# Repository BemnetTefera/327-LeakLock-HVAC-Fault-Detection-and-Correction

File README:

# LeakLock – Smart HVAC Fault Detection & Correction System

**LeakLock** is a low-cost, real-time HVAC monitoring solution that detects air duct leaks and corrects airflow across a three-zone system. Built with an ESP32, distributed sensors, and a web interface, it combines embedded systems, IoT, and sustainable design principles to solve a real-world energy efficiency problem.

---

## 🔧 Features

- 📶 Wi-Fi-enabled ESP32 microcontroller
- 🌡️ Real-time temperature and pressure sensing
- 🌀 Dual fan and motorized damper control
- 🖥️ Custom web interface using HTML, CSS, and JavaScript
- 🔄 OTA (Over-the-Air) updates for remote firmware management
- 🧩 PCB design files for sensor integration
- 📦 Total cost under $50

---

## 📁 Repository Structure

| File/Folder              | Description                                       |
|--------------------------|---------------------------------------------------|
| `index.html`             | Web interface frontend                           |
| `style.css`              | Styling for the frontend                         |
| `server.py`              | Tornado-based WebSocket server backend           |
| `main.cpp`               | ESP32 firmware: sensor reading & motor control   |
| `wifi_manager.cpp/h`     | Wi-Fi connection handler                         |
| `sensor_final_v1.brd`    | PCB board layout (EAGLE)                         |
| `sensor_final_v1.sch`    | PCB schematic (EAGLE)                            |
| `README.md`              | This file 📄                                     |

---

## ⚙️ How It Works

1. Sensors collect pressure and temperature data from three duct zones.
2. ESP32 processes this data and communicates with a web dashboard over Wi-Fi.
3. Based on detected anomalies (e.g., pressure drop), the system adjusts fans and damper positions to maintain balance.
4. The user can monitor and override controls via the web interface.
5. Updates can be deployed remotely via OTA.

---

## 🚀 Getting Started

### Requirements

- ESP32 Dev Module
- TMP102 Temperature Sensor(s)
- LPS25HB Pressure Sensor(s)
- TB6612FNG Dual H-Bridge Motor Driver
- Servo Motor (for damper control)
- 3D-printed or physical duct model (optional)
- Tornado (Python backend)
- EAGLE (for PCB design)

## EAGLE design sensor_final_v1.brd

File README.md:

# LeakLock – Smart HVAC Fault Detection & Correction System

**LeakLock** is a low-cost, real-time HVAC monitoring solution that detects air duct leaks and corrects airflow across a three-zone system. Built with an ESP32, distributed sensors, and a web interface, it combines embedded systems, IoT, and sustainable design principles to solve a real-world energy efficiency problem.

---

# 📄 [Full Design Description (Click Here)](description.md)

## 🔧 Features

- 📶 Wi-Fi-enabled ESP32 microcontroller
- 🌡️ Real-time temperature and pressure sensing
- 🌀 Dual fan and motorized damper control
- 🖥️ Custom web interface using HTML, CSS, and JavaScript
- 🔄 OTA (Over-the-Air) updates for remote firmware management
- 🧩 PCB design files for sensor integration
- 📦 Total cost under $50

---

## 📁 Repository Structure

| File/Folder              | Description                                       |
|--------------------------|---------------------------------------------------|
| `index.html`             | Web interface frontend                           |
| `style.css`              | Styling for the frontend                         |
| `server.py`              | Tornado-based WebSocket server backend           |
| `main.cpp`               | ESP32 firmware: sensor reading & motor control   |
| `wifi_manager.cpp/h`     | Wi-Fi connection handler                         |
| `sensor_final_v1.brd`    | PCB board layout (EAGLE)                         |
| `sensor_final_v1.sch`    | PCB schematic (EAGLE)                            |
| `README.md`              | This file 📄                                     |

---

## ⚙️ How It Works

1. Sensors collect pressure and temperature data from three duct zones.
2. ESP32 processes this data and communicates with a web dashboard over Wi-Fi.
3. Based on detected anomalies (e.g., pressure drop), the system adjusts fans and damper positions to maintain balance.
4. The user can monitor and override controls via the web interface.
5. Updates can be deployed remotely via OTA.

---

## 🚀 Requirements

- ESP32 Dev Module
- TMP102 Temperature Sensor(s)
- LPS25HB Pressure Sensor(s)
- TB6612FNG Dual H-Bridge Motor Driver
- Servo Motor (for damper control)
- 3D-printed or physical duct model (optional)
- Tornado (Python backend)
- EAGLE (for PCB design)

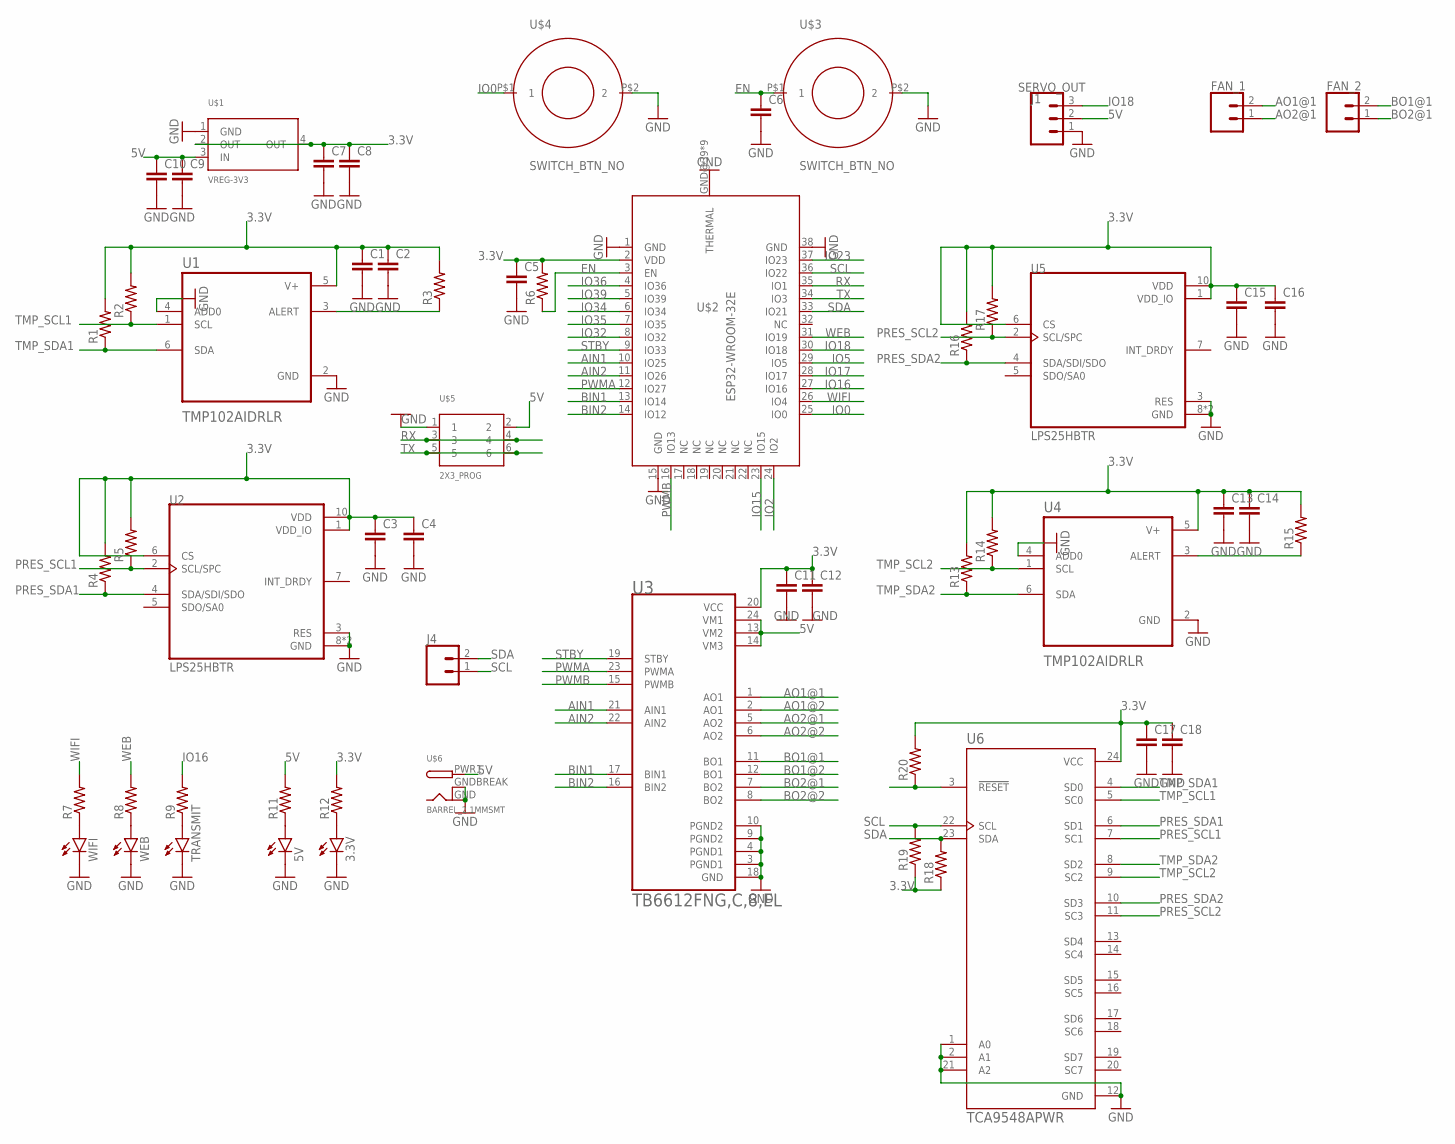
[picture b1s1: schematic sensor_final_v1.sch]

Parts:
3.3V, 5V: LEDSMT1206; 1206
C1, C2, C3, C4, C5, C6, C7, C8, C9, C10, C11, C12, C13, C14, C15, C16, C17, C18: CAP; 0805
FAN_1, FAN_2: CONN_02; 1X02
J1: SERVO_OUT; 1X03
J4: CONN_02; 1X02
R1, R2, R3, R4, R5, R6, R7, R8, R9, R11, R12, R13, R14, R15, R16, R17, R18, R19, R20: RES; 0805
TRANSMIT: LEDSMT1206; 1206
U1, U4: TMP102AIDRLR; SOT50P160X60-6N
U2, U5: LPS25HBTR; PQFN60P250X250X80-10N
U3: TB6612FNG,C,8,EL; SOP65P760X160-24N
U6: TCA9548APWR; SOP65P640X120-24N
U$1: VREG-3V3; R-PDSO-G4_TI
U$2: ESP32-WROOM-32E
U$3, U$4: SWITCH_BTN_NO; BTN_2
U$5: 2X3_PROG; 2X3_0.1IN
U$6: BARREL_2.1MMSMT; DCJACK_2MM_SMT
WEB: LEDSMT1206; 1206
WIFI: LEDSMT1206; 1206

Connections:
3.3V: C1.1, C2.1, C3.1, C4.1, C5.1, C7.1, C8.1, C11.1, C12.1, C13.1, C14.1, C15.1, C16.1, C17.1, C18.1, R1.2, R2.2, R3.2, R4.2, R5.2, R6.2, R12.2, R13.2, R14.2, R15.2, R16.2, R17.2, R18.1, R19.1, R20.2, U1.5 (V+), U2.1 (VDD_IO), U2.6 (CS), U2.10 (VDD), U3.20 (VCC), U4.5 (V+), U5.1 (VDD_IO), U5.6 (CS), U5.10 (VDD), U6.24 (VCC), U$1.2 (OUT), U$1.4 (OUT), U$2.2 (VDD)
5V: C9.1, C10.1, J1.2, R11.2, U3.13 (VM2), U3.14 (VM3), U3.24 (VM1), U$1.3 (IN), U$5.2, U$6.PWR1 (PWR)
AIN1: U3.21 (AIN1), U$2.10 (IO25)
AIN2: U3.22 (AIN2), U$2.11 (IO26)
AO1@1: FAN_1.2, U3.1 (AO1)
AO1@2: U3.2 (AO1)
AO2@1: FAN_1.1, U3.5 (AO2)
AO2@2: U3.6 (AO2)
BIN1: U3.17 (BIN1), U$2.13 (IO14)
BIN2: U3.16 (BIN2), U$2.14 (IO12)
BO1@1: FAN_2.2, U3.11 (BO1)
BO1@2: U3.12 (BO1)
BO2@1: FAN_2.1, U3.7 (BO2)
BO2@2: U3.8 (BO2)
EN: C6.1, R6.1, U$2.3 (EN), U$3.P$1 (1)
GND: 3.3V.C, 5V.C, C1.2, C2.2, C3.2, C4.2, C5.2, C6.2, C7.2, C8.2, C9.2, C10.2, C11.2, C12.2, C13.2, C14.2, C15.2, C16.2, C17.2, C18.2, J1.1, TRANSMIT.C, U1.2 (GND), U1.4 (ADD0), U2.3 (RES), U2.8 (GND), U2.9 (GND), U3.3 (PGND1), U3.4 (PGND1), U3.9 (PGND2), U3.10 (PGND2), U3.18 (GND), U4.2 (GND), U4.4 (ADD0), U5.3 (RES), U5.8 (GND), U5.9 (GND), U6.1 (A0), U6.2 (A1), U6.12 (GND), U6.21 (A2), U$1.1 (GND), U$2.1 (GND), U$2.15 (GND), U$2.38 (GND), U$2.GND@39 (THERMAL), U$2.GND@40 (THERMAL), U$2.GND@41 (THERMAL), U$2.GND@42 (THERMAL), U$2.GND@43 (THERMAL), U$2.GND@44 (THERMAL), U$2.GND@45 (THERMAL), U$2.GND@46 (THERMAL), U$2.GND@47 (THERMAL), U$3.P$2 (2), U$4.P$2 (2), U$5.1, U$6.GND, U$6.GNDBREAK, WEB.C, WIFI.C
IO0: U$2.25 (IO0), U$4.P$1 (1)
IO2: U$2.24 (IO2)
IO5: U$2.29 (IO5)
IO15: U$2.23 (IO15)
IO16: R9.2, U$2.27 (IO16)
IO17: U$2.28 (IO17)
IO18: J1.3, U$2.30 (IO18)
IO23: U$2.37 (IO23)
IO32: U$2.8 (IO32)
IO34: U$2.6 (IO34)
IO35: U$2.7 (IO35)
IO36: U$2.4 (IO36)
IO39: U$2.5 (IO39)
unnamed: R20.1, U6.3 (!RESET)
unnamed: R3.1, U1.3 (ALERT)
unnamed: R7.1, WIFI.A
unnamed: R8.1, WEB.A
unnamed: R9.1, TRANSMIT.A
unnamed: 5V.A, R11.1
unnamed: 3.3V.A, R12.1
unnamed: R15.1, U4.3 (ALERT)
PRES_SCL1: R5.1, U2.2 (SCL/SPC), U6.7 (SC1)
PRES_SCL2: R17.1, U5.2 (SCL/SPC), U6.11 (SC3)
PRES_SDA1: R4.1, U2.4 (SDA/SDI/SDO), U6.6 (SD1)
PRES_SDA2: R16.1, U5.4 (SDA/SDI/SDO), U6.10 (SD3)
PWMA: U3.23 (PWMA), U$2.12 (IO27)
PWMB: U3.15 (PWMB), U$2.16 (IO13)
RX: U$2.35 (IO1), U$5.3, U$5.4
SCL: J4.1, R19.2, U6.22 (SCL), U$2.36 (IO22)
SDA: J4.2, R18.2, U6.23 (SDA), U$2.33 (IO21)
STBY: U3.19 (STBY), U$2.9 (IO33)
TMP_SCL1: R2.1, U1.1 (SCL), U6.5 (SC0)
TMP_SCL2: R14.1, U4.1 (SCL), U6.9 (SC2)
TMP_SDA1: R1.1, U1.6 (SDA), U6.4 (SD0)
TMP_SDA2: R13.1, U4.6 (SDA), U6.8 (SD2)
TX: U$2.34 (IO3), U$5.5, U$5.6
WEB: R8.2, U$2.31 (IO19)
WIFI: R7.2, U$2.26 (IO4)

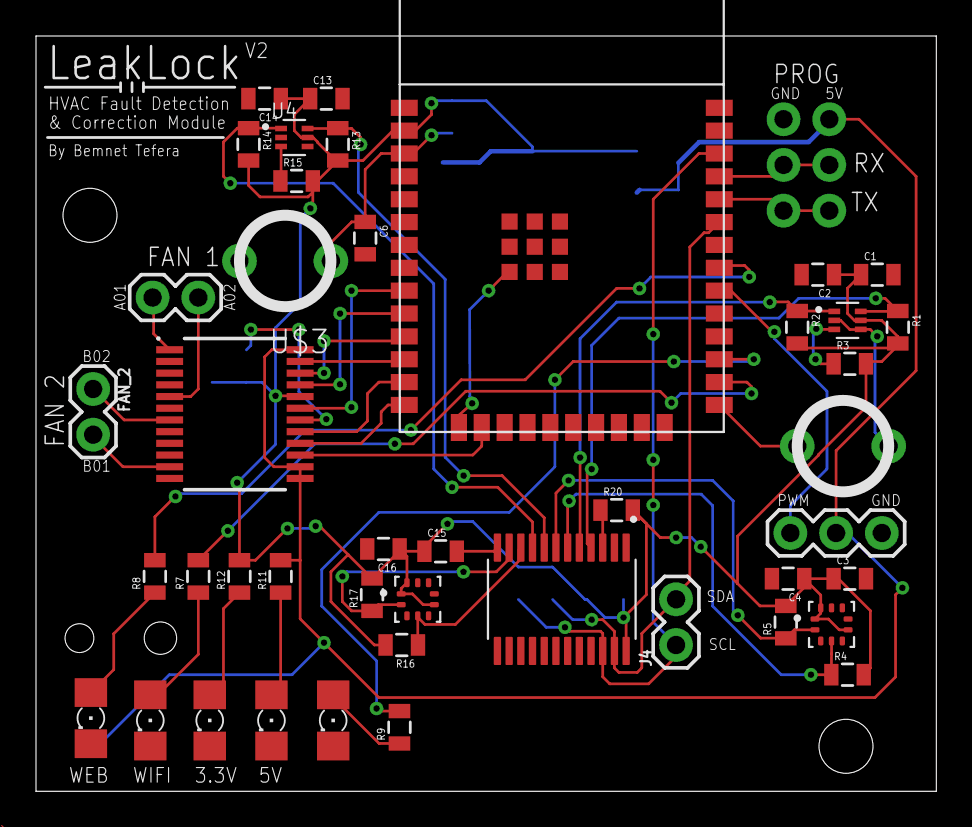
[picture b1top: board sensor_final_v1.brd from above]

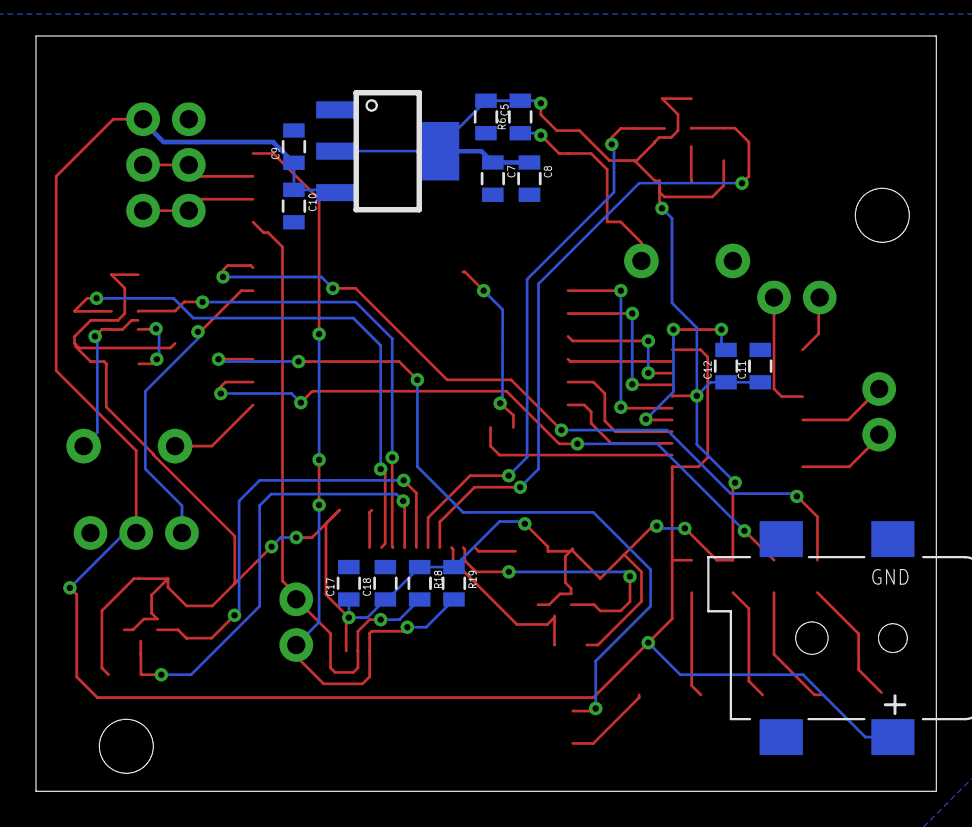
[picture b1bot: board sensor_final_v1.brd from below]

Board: 2 copper layers, 50.0 x 42.0 mm, 58 parts (14 on the bottom side), 40 nets.

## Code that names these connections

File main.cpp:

// ========== ESP32 HVAC FIRMWARE (Rewritten) ==========
#include <Arduino.h>
#include <Wire.h>
#include <WebSocketsClient.h>
#include <ArduinoJson.h>
#include "wifi_manager.h"

#define DEVICE_ID "zone2"  // Change this per ESP32: zone1, zone2, zone3
#define TMP102_ADDR 0x48
#define LPS25HB_ADDR 0x5D
#define TCA_ADDR 0x70

// Fan control
#define AIN1 25
#define AIN2 26
#define PWMA 27
#define BIN1 14
#define BIN2 12
#define PWMB 13
#define STBY 33
#define PWM_CHANNEL_A 0
#define PWM_CHANNEL_B 1
#define PWM_FREQ 1000
#define PWM_RES 8

// Servo
#define SERVO_PIN 18
#define PWM_CHANNEL_SERVO 2
#define SERVO_FREQ 50

// LEDs
#define WIFI_LED 4
#define WS_LED 19

// WebSocket target
const char* websocket_host = "192.168.12.211";
const uint16_t websocket_port = 8888;
const char* websocket_path = "/ws_esp32";

// State
int damperAngle = 90, lastDamperAngle = -1;
bool fanForward = true;
uint8_t fanSpeed = 128;
bool wifiConnected = false;
bool wsConnected = false;

WebSocketsClient webSocket;

// Tasks
TaskHandle_t h_sensorTask, h_webSocketTask, h_damperTask;

void tcaSelect(uint8_t channel) {
  if (channel > 7) return;
  Wire.beginTransmission(TCA_ADDR);
  Wire.write(1 << channel);
  Wire.endTransmission();
}

void applyFanSettings() {
  digitalWrite(STBY, HIGH);
  if (fanForward) {
    digitalWrite(BIN1, LOW); digitalWrite(BIN2, LOW); ledcWrite(PWM_CHANNEL_B, 0);
    digitalWrite(AIN1, HIGH); digitalWrite(AIN2, LOW); ledcWrite(PWM_CHANNEL_A, fanSpeed);
  } else {
    digitalWrite(AIN1, LOW); digitalWrite(AIN2, LOW); ledcWrite(PWM_CHANNEL_A, 0);
    digitalWrite(BIN1, HIGH); digitalWrite(BIN2, LOW); ledcWrite(PWM_CHANNEL_B, fanSpeed);
  }
}

void webSocketEvent(WStype_t type, uint8_t * payload, size_t length) {
  if (type == WStype_CONNECTED) {
    wsConnected = true;
    // Send handshake with device_id
    DynamicJsonDocument doc(64);
    doc["device_id"] = DEVICE_ID;
    String handshake;
    serializeJson(doc, handshake);
    webSocket.sendTXT(handshake);
  }
  else if (type == WStype_DISCONNECTED) wsConnected = false;

  if (type == WStype_TEXT) {
    DynamicJsonDocument doc(256);
    DeserializationError error = deserializeJson(doc, payload);
    if (error || !doc.containsKey("control")) return;
    if (doc["device_id"] != DEVICE_ID) return;

    String control = doc["control"];
    if (control == "speed") fanSpeed = doc["value"];
    else if (control == "direction") {
    String direction = doc["value"].as<String>();
    fanForward = (direction == "forward");
    } else if (control == "angle") damperAngle = constrain(doc["value"], 0, 180);
    applyFanSettings();
  }
}

float readTemperature(uint8_t ch) {
  tcaSelect(ch);
  Wire.beginTransmission(TMP102_ADDR);
  Wire.write(0x00);
  if (Wire.endTransmission() != 0) return 999;
  Wire.requestFrom(TMP102_ADDR, 2);
  if (Wire.available() < 2) return 999;
  int16_t raw = (Wire.read() << 4) | (Wire.read() >> 4);
  if (raw > 0x7FF) raw |= 0xF000;
  return raw * 0.0625 - 7.8;
}

float readPressure(uint8_t ch) {
  tcaSelect(ch);
  Wire.beginTransmission(LPS25HB_ADDR);
  Wire.write(0x28 | 0x80);
  if (Wire.endTransmission() != 0) return 999;
  Wire.requestFrom(LPS25HB_ADDR, 3);
  if (Wire.available() < 3) return 999;
  uint32_t raw = Wire.read();
  raw |= (Wire.read() << 8);
  raw |= (Wire.read() << 16);
  return raw / 4096.0 + 57;
}

void setServoAngle(int angle) {
  uint32_t duty = map(angle, 0, 180, 1638, 8192);
  ledcWrite(PWM_CHANNEL_SERVO, duty);
}

void sensorTask(void* pvParams) {
  while (true) {
    float t1 = readTemperature(0), t2 = readTemperature(2);
    float p1 = readPressure(1), p2 = readPressure(3);
    float avgT = (t1 + t2) / 2.0;
    float avgP = (p1 + p2) / 2.0;

    DynamicJsonDocument doc(256);
    doc["device_id"] = DEVICE_ID;
    doc["temp"] = avgT;
    doc["pressure"] = avgP;
    doc["fan_speed"] = fanSpeed;
    doc["fan_direction"] = fanForward ? "forward" : "reverse";
    doc["damper_angle"] = damperAngle;

    String msg;
    serializeJson(doc, msg);
    if (webSocket.isConnected()) webSocket.sendTXT(msg);
    vTaskDelay(500 / portTICK_PERIOD_MS);
  }
}

void webSocketTask(void* pvParams) {
  while (true) {
    webSocket.loop();
    handleOTA();
    vTaskDelay(50 / portTICK_PERIOD_MS);
  }
}

void damperTask(void* pvParams) {
  while (true) {
    if (abs(damperAngle - lastDamperAngle) >= 2) {
      setServoAngle(damperAngle);
      lastDamperAngle = damperAngle;
    }
    vTaskDelay(100 / portTICK_PERIOD_MS);
  }
}

void ledTask(void* pvParams) {
  unsigned long prevMillisWiFi = millis();
  unsigned long prevMillisWS = millis();
  bool wifiLedState = false;
  bool wsLedState = false;

  while (true) {
    unsigned long now = millis();

    // WIFI_LED: toggle every 125ms (2 times per second)
    if (now - prevMillisWiFi >= 1000) {
      prevMillisWiFi = now;
      wifiLedState = !wifiLedState;
      digitalWrite(WIFI_LED, wifiLedState);
    }

    // WS_LED: toggle every 250ms (1/4 second)
    if (now - prevMillisWS >= 250) {
      prevMillisWS = now;
      wsLedState = !wsLedState;
      digitalWrite(WS_LED, wsLedState);
    }

    vTaskDelay(10 / portTICK_PERIOD_MS);  // Prevent busy loop
  }
}


void setup() {
  Serial.begin(115200);
  Wire.begin(21, 22);
  pinMode(AIN1, OUTPUT); pinMode(AIN2, OUTPUT); pinMode(PWMA, OUTPUT);
  pinMode(BIN1, OUTPUT); pinMode(BIN2, OUTPUT); pinMode(PWMB, OUTPUT);
  pinMode(STBY, OUTPUT); digitalWrite(STBY, HIGH);
  pinMode(WIFI_LED, OUTPUT); pinMode(WS_LED, OUTPUT);

  ledcSetup(PWM_CHANNEL_A, PWM_FREQ, PWM_RES); ledcAttachPin(PWMA, PWM_CHANNEL_A);
  ledcSetup(PWM_CHANNEL_B, PWM_FREQ, PWM_RES); ledcAttachPin(PWMB, PWM_CHANNEL_B);
  ledcSetup(PWM_CHANNEL_SERVO, SERVO_FREQ, 16); ledcAttachPin(SERVO_PIN, PWM_CHANNEL_SERVO);
  setServoAngle(damperAngle);
  applyFanSettings();

  for (int ch : {1, 3}) {
    tcaSelect(ch);
    Wire.beginTransmission(LPS25HB_ADDR);
    Wire.write(0x20); Wire.write(0b11000000); Wire.endTransmission();
  }

  printMacAddress();
  connectToWiFiAndStartOTA();
  wifiConnected = true;

  webSocket.begin(websocket_host, websocket_port, websocket_path);
  webSocket.onEvent(webSocketEvent);
  webSocket.setReconnectInterval(5000);

  xTaskCreatePinnedToCore(sensorTask,    "Sensor",    4096, NULL, 2, &h_sensorTask,    1);
  xTaskCreatePinnedToCore(webSocketTask, "WebSocket", 2048, NULL, 1, &h_webSocketTask, 1);
  xTaskCreatePinnedToCore(damperTask,    "Damper",    2048, NULL, 1, &h_damperTask,    1);
  xTaskCreatePinnedToCore(ledTask,       "LED",       1024, NULL, 1, NULL,             0);
}

void loop() {}

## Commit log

2025-06-15 Add files via upload
    USER GUIDE:
    Software:
    ** Make sure to prepare local host by running the torando server using the "server.py".
    ** In the same folder as server.py include a folder that contains both the index.html and the style.css file. (Do this prior to running the server file)
    ** To each ESP32 module upload the main.cpp using platform io. Note that wifi_manager.cpp and wifi_manager.h must be in the same project folder and workspace as the main.cpp
    Hardware:
2025-06-15 Create Read
2025-06-15 main.cpp
2025-06-15 wifi_manager.cpp
2025-06-15 wifi_manager.h
2025-06-15 index.hmtl
2025-06-15 style.css
2025-06-15 server.py
2025-06-15 README
2025-06-15 README.md
2025-06-15 DESCRIPTION.md
2025-06-15 \DESCRIPTION.md

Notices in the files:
parts and their libraries:
SparkFun-Connectors: Licensing: Creative Commons ShareAlike 4.0 International - https://creativecommons.org/licenses/by-sa/4.0
